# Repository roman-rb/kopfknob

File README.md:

# kopfknob
A simple Arduino program to turn a knob

This program controls a small DC gearmotor with encoder (DFRobot FIT0485), turning it at a constant speed defined by user input through an OLED screen and encoder knob with
the help of an H-Bridge Driver IC (L293D).

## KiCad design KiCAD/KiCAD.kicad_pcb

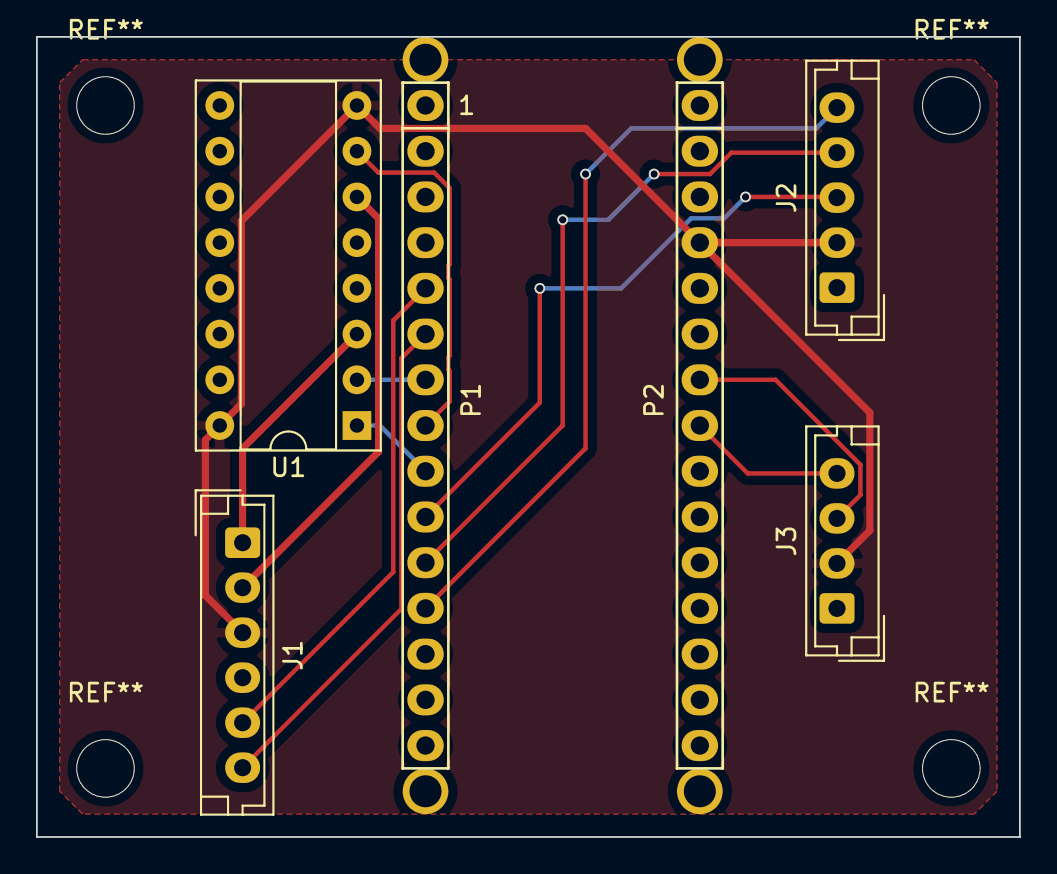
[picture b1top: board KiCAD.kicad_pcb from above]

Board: 2 copper layers, 54.6 x 44.5 mm, 10 parts (0 on the bottom side), 15 nets.

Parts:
J1: Motor Conn.; JST_EH_B6B-EH-A_1x06_P2.50mm_Vertical
J2: Encoder Conn.; JST_EH_B5B-EH-A_1x05_P2.50mm_Vertical
J3: OLED Conn.; JST_EH_B4B-EH-A_1x04_P2.50mm_Vertical
P1: Digital; Socket_Strip_Arduino_1x15
P2: Analog; Socket_Strip_Arduino_1x15
P3, P4, P5, P6: CONN_01X01; 1pin_Nano
U1: L293D; DIP-16_W7.62mm_Socket

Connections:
+5V: J1.3, J2.2, J3.2, P2.4, U1.8, U1.16
/2: J1.5, P1.5
/3(**): J1.6, P1.6
/4: P1.7, U1.2
/5(**): P1.8, U1.7
/6(**): P1.9, U1.1
/7: J2.3, P1.10
/8: J2.4, P1.11
/9(**): J2.5, P1.12
/A4: J3.4, P2.8
/A5: J3.3, P2.7
/Reset: P1.3, P2.3
GND: J1.4, J2.1, J3.1, P1.4, P2.2, U1.4, U1.5, U1.12, U1.13
unnamed: J1.1, U1.3
unnamed: J1.2, U1.6

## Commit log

2020-07-18 Add existing PlatformIO code
2020-07-30 Added PCB Files
2020-08-10 Rewrite for DC Gearmotor With Encoder
    * Added code to run FIT0485 Gearmotor from Digikey
    * Added code to take input from a rotary encoder knob w/ pushbutton
    * Changed UI on OLED Screen
    * Added basic input debugging through serial port (commented out for production)
